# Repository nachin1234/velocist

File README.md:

Este proyecto consta de un seguidor de lineas hecho con un ESP-32 y micromotores pololu.
Integrantes: Soria Ignacio, Montaño Benjamin, Sachetti Thomas, Latrichana Milagros.

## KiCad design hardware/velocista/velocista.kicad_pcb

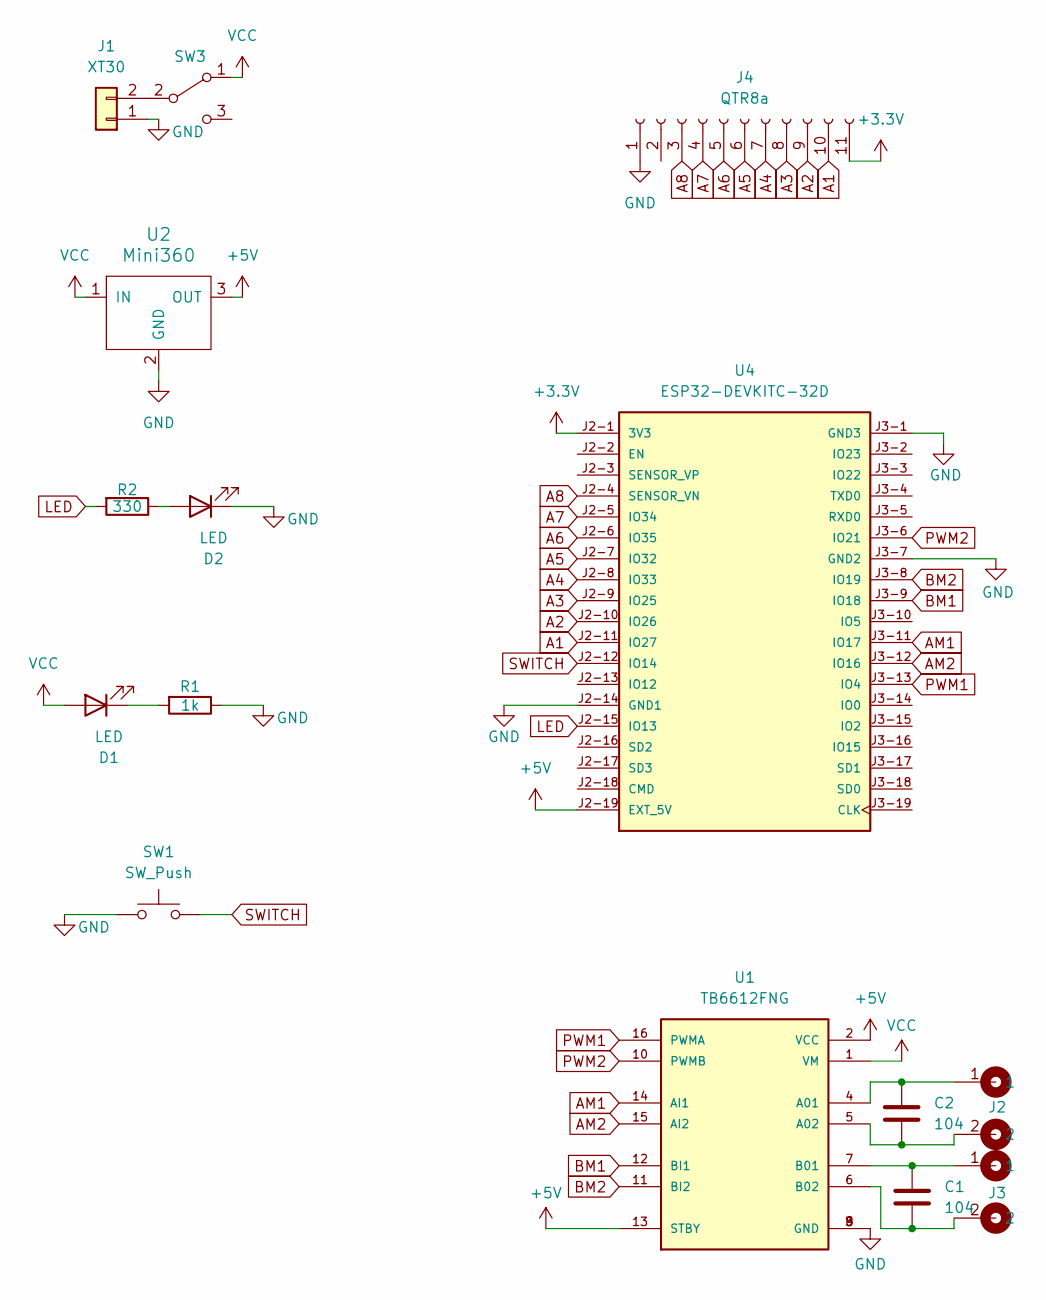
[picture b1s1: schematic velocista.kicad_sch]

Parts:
C1, C2: 104; C_0805_2012Metric
D1, D2: LED; led_5mm_green
J1: XT30; AMASS_XT30UPB-M_1x02_P5.0mm_Vertical
J2, J3: Cable_PAD; Cable-doble-THT
J4: QTR8a; JST_EH_S11B-EH_1x11_P2.50mm_Horizontal
R1: 1k; R_0805_2012Metric_Pad1.20x1.40mm_HandSolder
R2: 330; R_0805_2012Metric_Pad1.20x1.40mm_HandSolder
SW1: SW_Push; SW_PUSH_1P1T_6x3.5mm_H5.0_APEM_MJTP1250
SW3: SW_SPDT; SW_EG1247
U1: TB6612FNG; MODULE_ROB-14450; PARTREV 11-13-17
U2: Mini360; Mini360_step-down
U4: ESP32-DEVKITC-32D; MODULE_ESP32-DEVKITC-32D; PARTREV V4

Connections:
+3.3V: J4.11, U4.J2-1 (3V3)
+5V: U1.2 (VCC), U1.13 (STBY), U2.3 (OUT), U4.J2-19 (EXT_5V)
A1: J4.10, U4.J2-11 (IO27)
A2: J4.9, U4.J2-10 (IO26)
A3: J4.8, U4.J2-9 (IO25)
A4: J4.7, U4.J2-8 (IO33)
A5: J4.6, U4.J2-7 (IO32)
A6: J4.5, U4.J2-6 (IO35)
A7: J4.4, U4.J2-5 (IO34)
A8: J4.3, U4.J2-4 (SENSOR_VN)
AM1: U1.14 (AI1), U4.J3-11 (IO17)
AM2: U1.15 (AI2), U4.J3-12 (IO16)
BM1: U1.12 (BI1), U4.J3-9 (IO18)
BM2: U1.11 (BI2), U4.J3-8 (IO19)
GND: D2.1 (K), J1.1, J4.1, R1.1, SW1.1, U1.3 (GND), U1.8 (GND), U1.9 (GND), U2.2 (GND), U4.J2-14 (GND1), U4.J3-1 (GND3), U4.J3-7 (GND2)
LED: R2.2, U4.J2-15 (IO13)
unnamed: D1.1 (K), R1.2
unnamed: D2.2 (A), R2.1
unnamed: J1.2, SW3.2 (B)
unnamed: C2.1, J2.1, U1.4 (A01)
unnamed: C2.2, J2.2, U1.5 (A02)
unnamed: C1.2, J3.1, U1.7 (B01)
unnamed: C1.1, J3.2, U1.6 (B02)
PWM1: U1.16 (PWMA), U4.J3-13 (IO4)
PWM2: U1.10 (PWMB), U4.J3-6 (IO21)
SWITCH: SW1.2, U4.J2-12 (IO14)
VCC: D1.2 (A), SW3.1 (A), U1.1 (VM), U2.1 (IN)

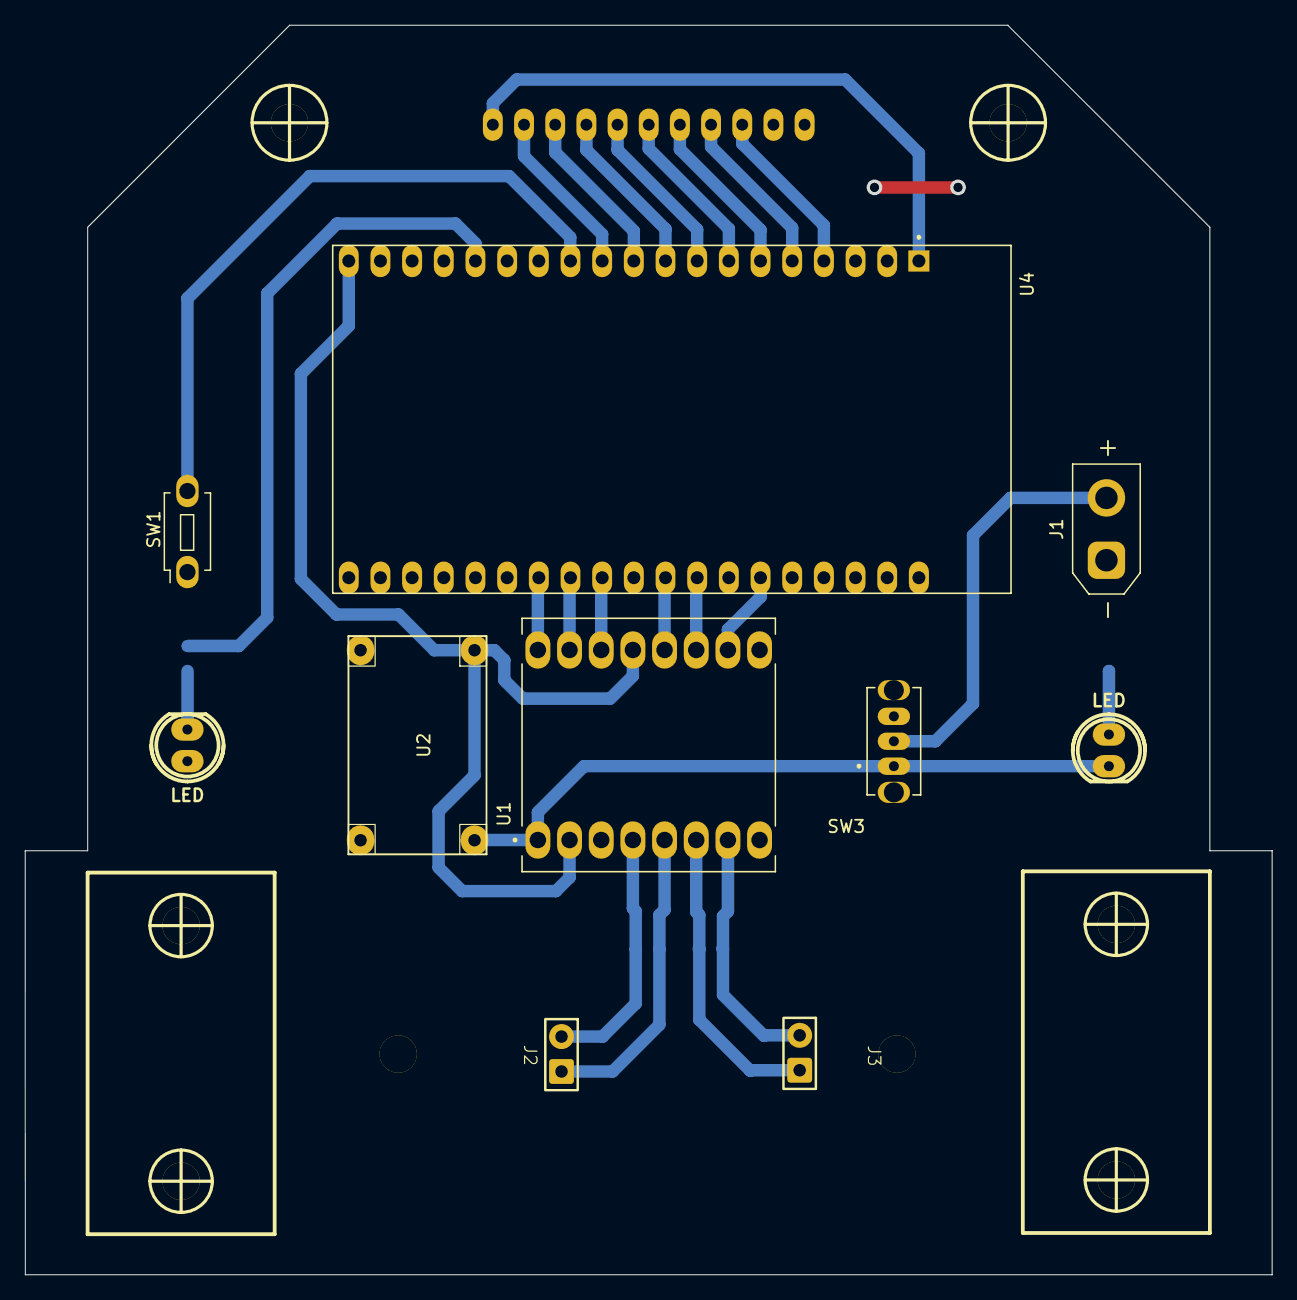
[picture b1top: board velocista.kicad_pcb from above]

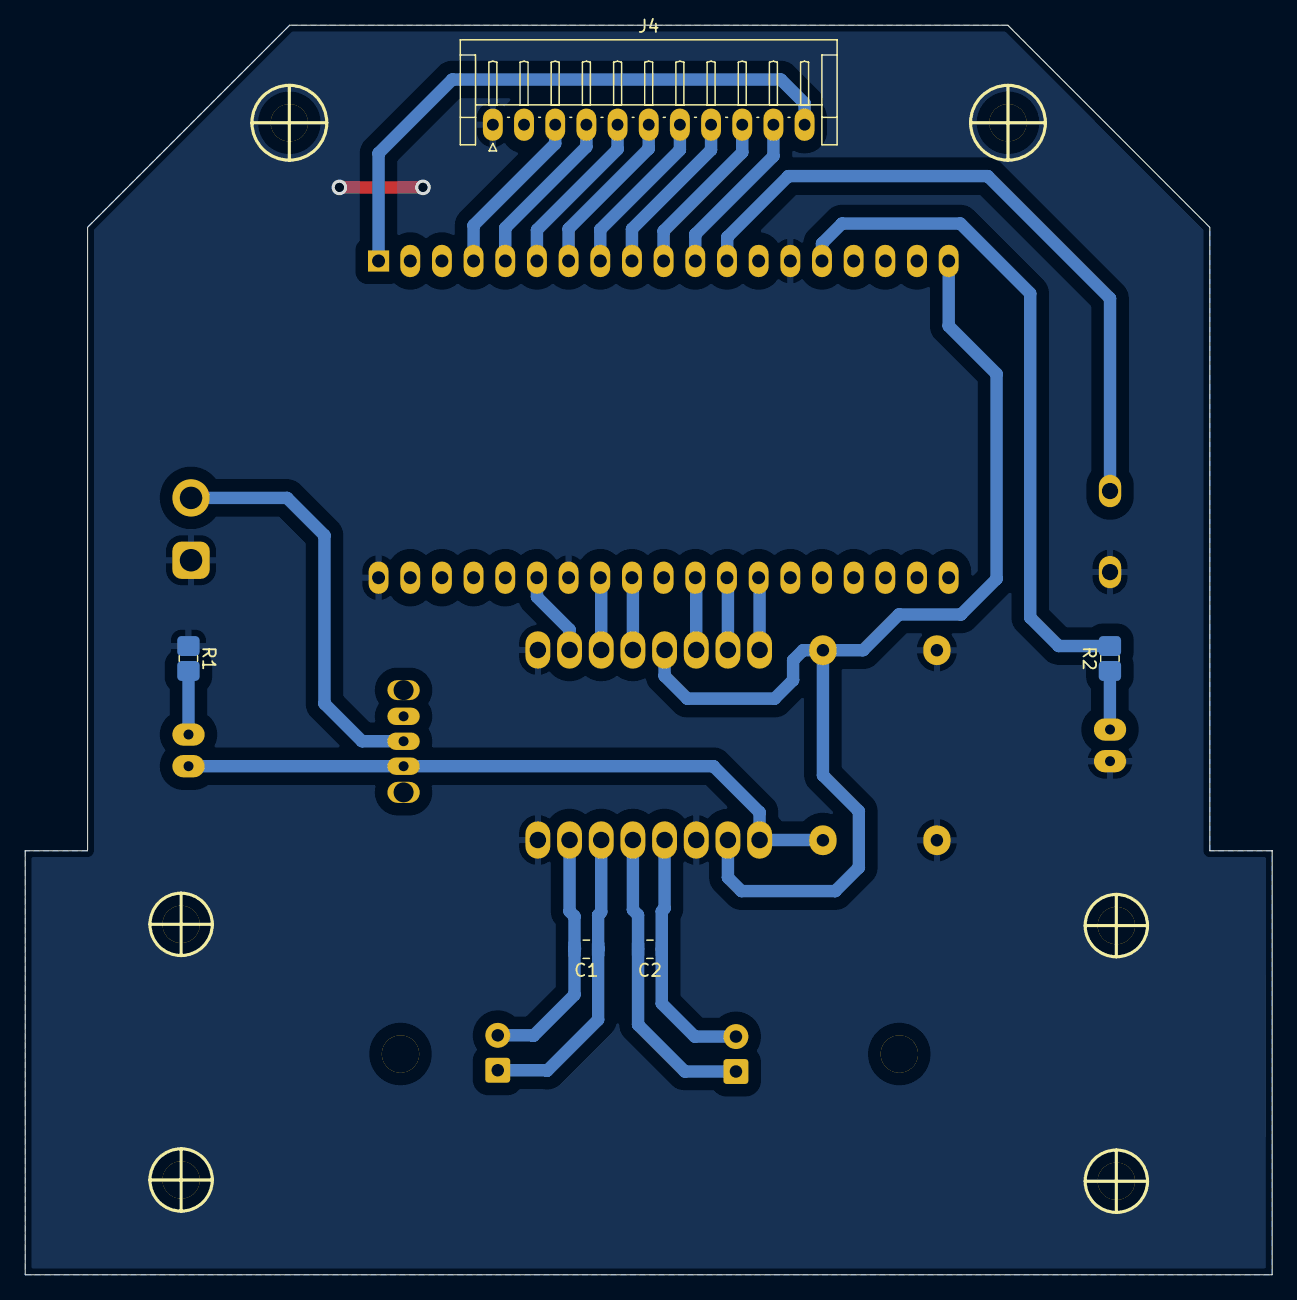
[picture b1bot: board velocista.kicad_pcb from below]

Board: 2 copper layers, 100.0 x 100.2 mm, 19 parts (5 on the bottom side), 27 nets.

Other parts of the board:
Pololu_Micro_Gear_Motor: VAL**; Pololu_Micro_Bracket_Wheel_42mm
Pololu_Micro_Gear_Motor#2: VAL**; Pololu_Micro_Bracket_Wheel_42mm
Tornillo_M3_8mm, Tornillo_M3_8mm#2: VAL**; Tornillo_M3_8mm

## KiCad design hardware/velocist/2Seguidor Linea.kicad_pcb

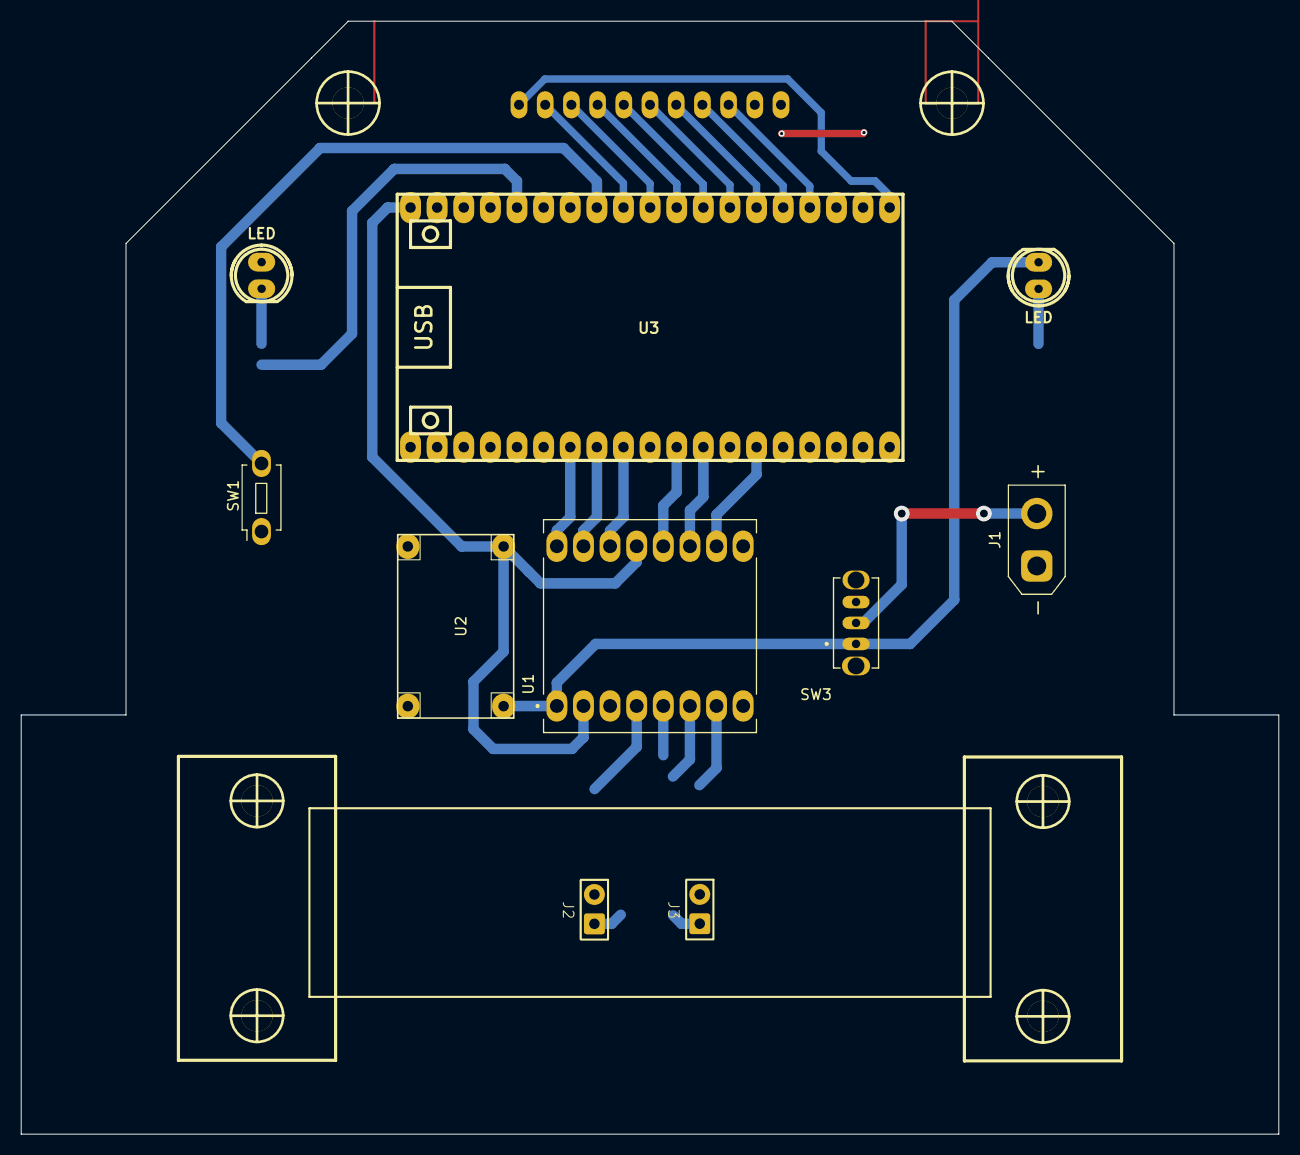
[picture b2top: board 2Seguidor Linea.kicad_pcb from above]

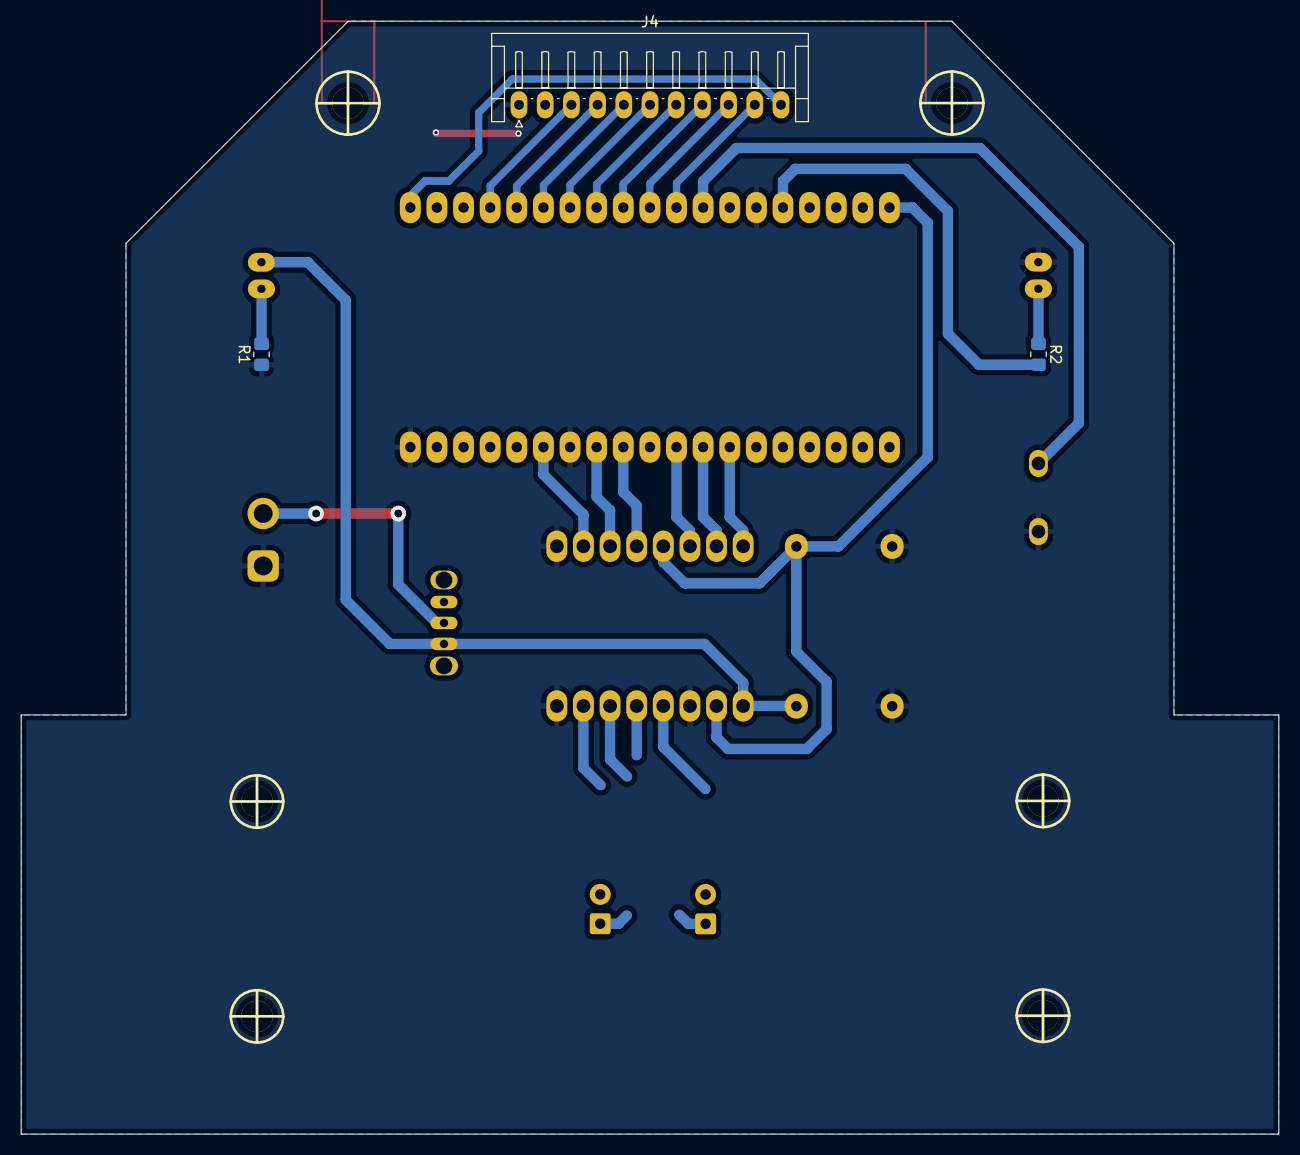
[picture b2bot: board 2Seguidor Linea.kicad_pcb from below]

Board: 2 copper layers, 120.0 x 106.2 mm, 17 parts (3 on the bottom side), 27 nets.

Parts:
D1, D2: LED; led_5mm_green
J1: XT30; AMASS_XT30UPB-M_1x02_P5.0mm_Vertical
J2, J3: Cable_PAD; Cable-doble-THT
J4: QTR8a; JST_EH_S11B-EH_1x11_P2.50mm_Horizontal
Pololu_Micro_Gear_Motor: VAL**; Pololu_Micro_Bracket_Wheel_42mm
Pololu_Micro_Gear_Motor#2: VAL**; Pololu_Micro_Bracket_Wheel_42mm
R1: 1k; R_0805_2012Metric_Pad1.20x1.40mm_HandSolder
R2: 330; R_0805_2012Metric_Pad1.20x1.40mm_HandSolder
SW1: SW_Push; SW_PUSH_1P1T_6x3.5mm_H5.0_APEM_MJTP1250
SW3: SW_SPDT; SW_EG1247
Tornillo_M3_8mm, Tornillo_M3_8mm#2: VAL**; Tornillo_M3_8mm
U1: TB6612FNG; MODULE_ROB-14450
U2: Mini360; Mini360_step-down
U3: ESP32_DEVKITC; ESP32S

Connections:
+3.3V: J4.11, U3.1 (3V3)
+5V: U1.2 (VCC), U1.13 (STBY), U2.3 (OUT), U3.19 (5V)
A1: J4.10, U3.11 (IO27)
A2: J4.9, U3.10 (IO26)
A3: J4.8, U3.9 (IO25)
A4: J4.7, U3.8 (IO33)
A5: J4.6, U3.7 (IO32)
A6: J4.5, U3.6 (IO35)
A7: J4.4, U3.5 (IO34)
A8: J4.3, U3.4 (SVN)
AM1: U1.14 (AI1), U3.28 (IO17)
AM2: U1.15 (AI2), U3.27 (IO16)
BM1: U1.12 (BI1), U3.30 (IO18)
BM2: U1.11 (BI2), U3.31 (IO19)
GND: D2.1 (K), J1.1, J4.1, R1.1, SW1.1, U1.3 (GND), U1.8 (GND), U1.9 (GND), U2.2 (GND), U3.14 (GND), U3.32 (GND), U3.38 (GND)
LED: R2.2, U3.15 (IO13)
unnamed: D1.1 (K), R1.2
unnamed: D2.2 (A), R2.1
unnamed: J1.2, SW3.2 (B)
unnamed: J2.1, U1.4 (A01)
unnamed: J2.2, U1.5 (A02)
unnamed: J3.1, U1.7 (B01)
unnamed: J3.2, U1.6 (B02)
PWM1: U1.16 (PWMA), U3.26 (IO4)
PWM2: U1.10 (PWMB), U3.33 (IO21)
SWITCH: SW1.2, U3.12 (IO14)
VCC: D1.2 (A), SW3.1 (A), U1.1 (VM), U2.1 (IN)

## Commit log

2026-03-31 Mi primer commit
2026-03-31 hardware añadido
2026-04-10 act pcb
2026-04-13 act placa
2026-04-13 act readme y placa
2026-04-15 remove
2026-04-21 act placa xd
2026-04-24 nueva act
2026-04-24 actu pcb
2026-04-28 modelos 3d
2026-05-05 act codigo
2026-05-08 act 3d
2026-05-11 act pads
2026-06-12 rele mili
